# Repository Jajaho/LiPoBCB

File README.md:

---
## Artifacts

[Docs](https://github.com/Jajaho/LiPoBCB/suites/9631889772/artifacts/460196864)  
[Images](https://github.com/Jajaho/LiPoBCB/suites/9631889772/artifacts/460196866)  
[CAD](https://github.com/Jajaho/LiPoBCB/suites/9631889772/artifacts/460196863)  
[Gerber](https://github.com/Jajaho/LiPoBCB/suites/9631889772/artifacts/460196865)

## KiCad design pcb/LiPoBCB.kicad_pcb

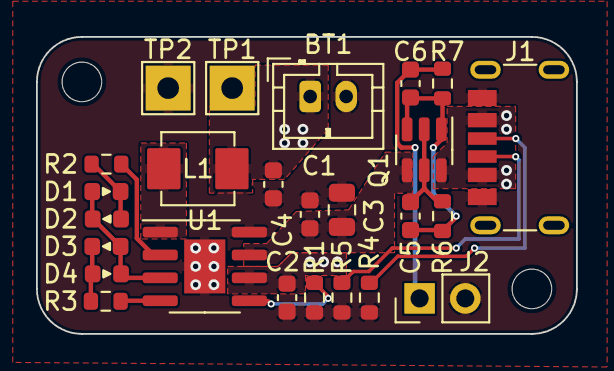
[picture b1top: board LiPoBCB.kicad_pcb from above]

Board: 2 copper layers, 30.0 x 16.5 mm, 27 parts (0 on the bottom side), 16 nets.

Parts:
BT1: Battery_Cell; JST_PH_B2B-PH-K_1x02_P2.00mm_Vertical
C1, C4: 10 uF; C_0603_1608Metric
C2: 4.7 uF; C_0603_1608Metric
C3: 22 uF; C_0805_2012Metric
C5, C6: 100n; C_0603_1608Metric
D1, D2, D3, D4: LED blue; D_0603_1608Metric
H1, H2: MountingHole; MountingHole_2.2mm_M2_ISO14580
J1: USB-C_6_pin_receptacle; Korean Hroparts Elec TYPE-C-31-M-17
J2: Conn_01x02; PinHeader_1x02_P2.54mm_Vertical
L1: 1 uH; L_smd_1616
Q1: Q_Dual_PMOS_S1G1D2S2G2D1; SOT-23-6
R1: R; R_0603_1608Metric
R2, R3: 1k; R_0603_1608Metric
R4, R5: 5K1; R_0603_1608Metric
R6: 100K; R_0603_1608Metric
R7: 10K; R_0603_1608Metric
TP1: 5V; TestPoint_THTPad_2.5x2.5mm_Drill1.2mm
TP2: GND; TestPoint_THTPad_2.5x2.5mm_Drill1.2mm
U1: ETA9740; SOIC-8-1EP_3.9x4.9mm_P1.27mm_EP2.29x3mm

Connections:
+5V: C1.1, C3.1, Q1.4 (D), U1.7 (OUT)
/BAT: BT1.1 (+), C2.1, C4.2, L1.2, U1.6 (BAT)
/CC1: J1.A5 (CC1), R5.1
/CC2: J1.B5 (CC2), R4.1
/ISET: R1.1, U1.5 (ISET)
/LED1: R2.1, U1.2 (LED1)
/LED2: D1.2 (A), D2.1 (K), D3.2 (A), D4.1 (K), U1.3 (LED2)
/LED3: R3.1, U1.4 (LED3)
/SW: L1.1, U1.1 (SW)
/SW_GATE: C5.2, C6.1, Q1.1 (G), Q1.3 (G), R6.2, R7.1
/VBUS: J1.A9 (VBUS), J1.B9 (VBUS), Q1.6 (D), TP1.1
GND: BT1.2 (-), C1.2, C2.2, C3.2, C4.1, J1.A12 (GND), J1.B12 (GND), J2.2, R1.2, R4.2, R5.2, TP2.1, U1.8 (PGND), U1.9 (AGND)
unnamed: C5.1, Q1.2 (S), Q1.5 (S), R6.1
unnamed: C6.2, J2.1, R7.2
unnamed: D1.1 (K), D2.2 (A), R2.2
unnamed: D3.1 (K), D4.2 (A), R3.2

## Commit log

2022-12-02 replaced pcb files
2022-12-03 Update pcb files
2022-12-03 Updates DRC
